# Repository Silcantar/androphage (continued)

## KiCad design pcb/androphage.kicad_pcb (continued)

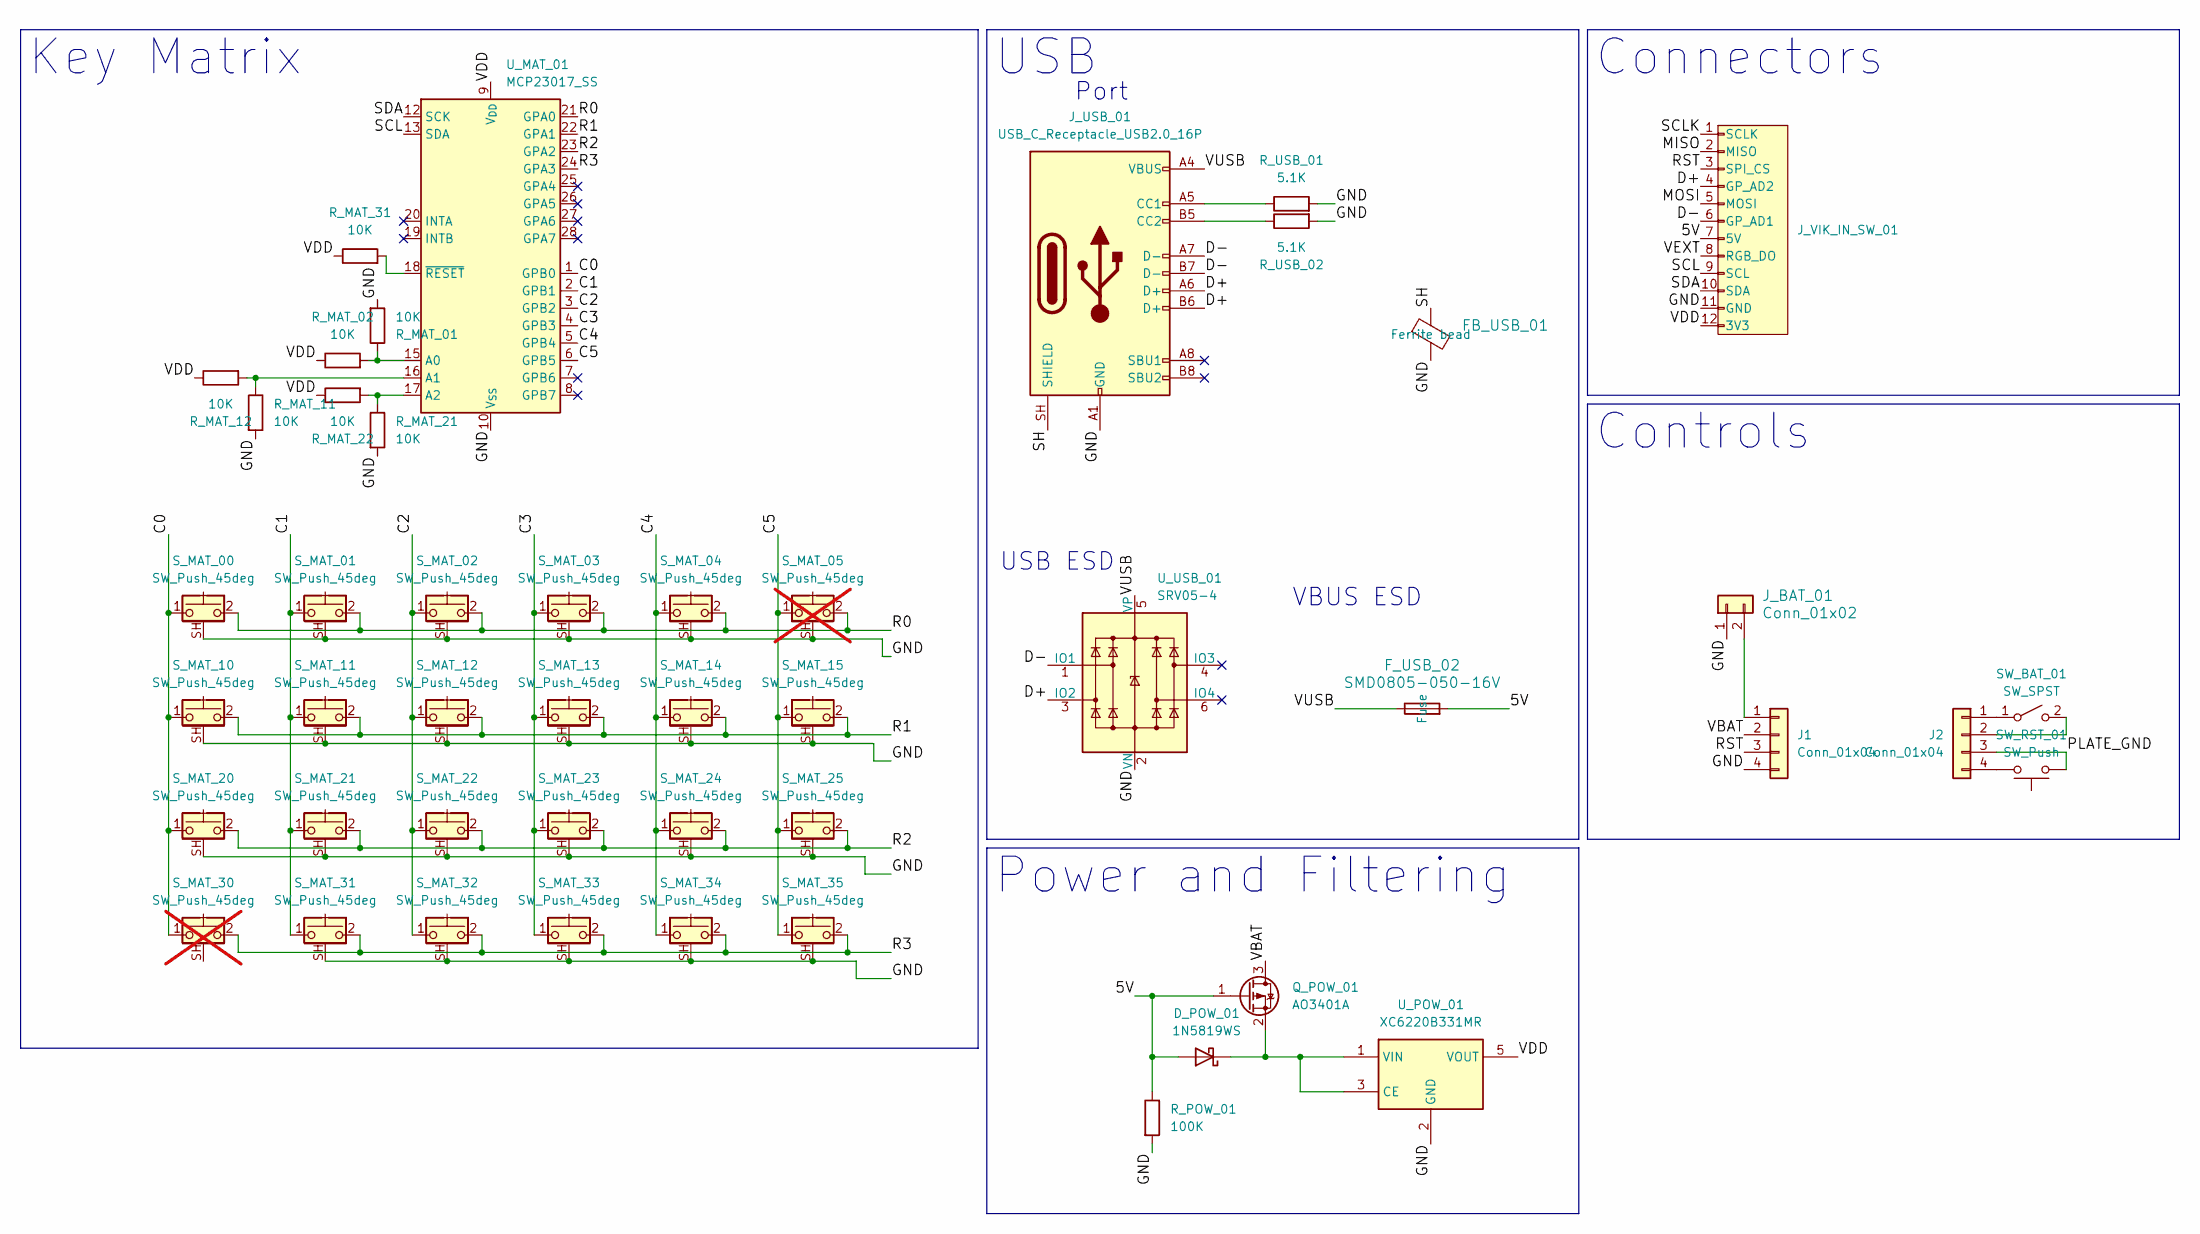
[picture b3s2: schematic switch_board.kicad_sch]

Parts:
D_POW_01: 1N5819WS; D_SOD-323
FB_USB_01: L_0805_2012Metric; LCSC Part Number C21286
F_USB_02: SMD0805-050-16V; Fuse_0805_2012Metric; Manufacturer Part Number SMD0805-050-16V; LCSC Part Number C2833485
J1, J2: Conn_01x04; PinHeader_1x04_P2.54mm_Vertical
J_BAT_01: Conn_01x02; JST_GH_SM02B-GHS-TB_1x02-1MP_P1.25mm_Horizontal
J_USB_01: USB_C_Receptacle_USB2.0_16P; USB_C_Receptacle_HRO_TYPE-C-31-M-12
J_VIK_IN_SW_01: vik-module-connector; vik-module-connector-horizontal
Q_POW_01: AO3401A; SOT-23
R_MAT_01, R_MAT_02, R_MAT_11, R_MAT_12, R_MAT_21, R_MAT_22, R_MAT_31: 10K; R_0201_0603Metric_Pad0.64x0.40mm_HandSolder
R_POW_01: 100K; R_0201_0603Metric_Pad0.64x0.40mm_HandSolder
R_USB_01, R_USB_02: 5.1K; R_0201_0603Metric_Pad0.64x0.40mm_HandSolder
SW_BAT_01: SW_SPST; AS11CH
SW_RST_01: SW_Push; SW_Push_1P1T_NO_E-Switch_TL3301NxxxxxG
S_MAT_00, S_MAT_01, S_MAT_02, S_MAT_03, S_MAT_04, S_MAT_10, S_MAT_11, S_MAT_12, S_MAT_13, S_MAT_14, S_MAT_15, S_MAT_20, S_MAT_21, S_MAT_22, S_MAT_23, S_MAT_24, S_MAT_25, S_MAT_31, S_MAT_32, S_MAT_33, S_MAT_34, S_MAT_35: SW_Push_45deg; SW_Kailh_Choc_V1V2_HotSwap_PTH_Double
S_MAT_05, S_MAT_30: SW_Push_45deg; SW_Kailh_Choc_V1V2_HotSwap_PTH_Double; not fitted
U_MAT_01: MCP23017_SS; SSOP-28_5.3x10.2mm_P0.65mm
U_POW_01: XC6220B331MR; SOT-23-5
U_USB_01: SRV05-4; SOT-23-6

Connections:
/Switch_Board/5V: D_POW_01.2 (A), F_USB_02.2, J_VIK_IN_SW_01.7 (5V), Q_POW_01.1 (G), R_POW_01.1
/Switch_Board/C0: S_MAT_00.1, S_MAT_10.1, S_MAT_20.1, S_MAT_30.1, U_MAT_01.1 (GPB0)
/Switch_Board/C1: S_MAT_01.1, S_MAT_11.1, S_MAT_21.1, S_MAT_31.1, U_MAT_01.2 (GPB1)
/Switch_Board/C2: S_MAT_02.1, S_MAT_12.1, S_MAT_22.1, S_MAT_32.1, U_MAT_01.3 (GPB2)
/Switch_Board/C3: S_MAT_03.1, S_MAT_13.1, S_MAT_23.1, S_MAT_33.1, U_MAT_01.4 (GPB3)
/Switch_Board/C4: S_MAT_04.1, S_MAT_14.1, S_MAT_24.1, S_MAT_34.1, U_MAT_01.5 (GPB4)
/Switch_Board/C5: S_MAT_05.1, S_MAT_15.1, S_MAT_25.1, S_MAT_35.1, U_MAT_01.6 (GPB5)
/Switch_Board/D+: J_USB_01.A6 (D+), J_USB_01.B6 (D+), J_VIK_IN_SW_01.4 (GP_AD2), U_USB_01.3 (IO2)
/Switch_Board/D-: J_USB_01.A7 (D-), J_USB_01.B7 (D-), J_VIK_IN_SW_01.6 (GP_AD1), U_USB_01.1 (IO1)
/Switch_Board/GND: FB_USB_01.2, J1.4, J_BAT_01.1, J_USB_01.A1 (GND), J_USB_01.A12 (GND), J_USB_01.B1 (GND), J_USB_01.B12 (GND), J_VIK_IN_SW_01.11 (GND), R_MAT_01.2, R_MAT_11.2, R_MAT_21.2, R_POW_01.2, R_USB_01.2, R_USB_02.2, S_MAT_00.SH (B), S_MAT_01.SH (B), S_MAT_02.SH (B), S_MAT_03.SH (B), S_MAT_04.SH (B), S_MAT_05.SH (B), S_MAT_10.SH (B), S_MAT_11.SH (B), S_MAT_12.SH (B), S_MAT_13.SH (B), S_MAT_14.SH (B), S_MAT_15.SH (B), S_MAT_20.SH (B), S_MAT_21.SH (B), S_MAT_22.SH (B), S_MAT_23.SH (B), S_MAT_24.SH (B), S_MAT_25.SH (B), S_MAT_31.SH (B), S_MAT_32.SH (B), S_MAT_33.SH (B), S_MAT_34.SH (B), S_MAT_35.SH (B), U_MAT_01.10 (V_{SS}), U_POW_01.2 (GND), U_USB_01.2 (VN)
/Switch_Board/MISO: J_VIK_IN_SW_01.2 (MISO)
/Switch_Board/MOSI: J_VIK_IN_SW_01.5 (MOSI)
/Switch_Board/PLATE_GND: J2.3, SW_RST_01.1
/Switch_Board/R0: S_MAT_00.2, S_MAT_01.2, S_MAT_02.2, S_MAT_03.2, S_MAT_04.2, S_MAT_05.2, U_MAT_01.21 (GPA0)
/Switch_Board/R1: S_MAT_10.2, S_MAT_11.2, S_MAT_12.2, S_MAT_13.2, S_MAT_14.2, S_MAT_15.2, U_MAT_01.22 (GPA1)
/Switch_Board/R2: S_MAT_20.2, S_MAT_21.2, S_MAT_22.2, S_MAT_23.2, S_MAT_24.2, S_MAT_25.2, U_MAT_01.23 (GPA2)
/Switch_Board/R3: S_MAT_30.2, S_MAT_31.2, S_MAT_32.2, S_MAT_33.2, S_MAT_34.2, S_MAT_35.2, U_MAT_01.24 (GPA3)
/Switch_Board/RST: J1.3, J_VIK_IN_SW_01.3 (SPI_CS)
/Switch_Board/SCL: J_VIK_IN_SW_01.9 (SCL), U_MAT_01.13 (SDA)
/Switch_Board/SCLK: J_VIK_IN_SW_01.1 (SCLK)
/Switch_Board/SDA: J_VIK_IN_SW_01.10 (SDA), U_MAT_01.12 (SCK)
/Switch_Board/SH: FB_USB_01.1, J_USB_01.SH (SHIELD)
/Switch_Board/VBAT: J1.2, Q_POW_01.3 (D)
/Switch_Board/VDD: J_VIK_IN_SW_01.12 (3V3), R_MAT_02.1, R_MAT_12.1, R_MAT_22.1, R_MAT_31.1, U_MAT_01.9 (V_{DD}), U_POW_01.5 (VOUT)
/Switch_Board/VEXT: J_VIK_IN_SW_01.8 (RGB_DO)
/Switch_Board/VUSB: F_USB_02.1, J_USB_01.A4 (VBUS), J_USB_01.A9 (VBUS), J_USB_01.B4 (VBUS), J_USB_01.B9 (VBUS), U_USB_01.5 (VP)
unnamed: D_POW_01.1 (K), Q_POW_01.2 (S), U_POW_01.1 (VIN), U_POW_01.3 (CE)
unnamed: J1.1, J_BAT_01.2
unnamed: J2.1, SW_BAT_01.1 (A)
unnamed: J2.2, SW_BAT_01.2 (B)
unnamed: J2.4, SW_RST_01.2
unnamed: J_USB_01.A5 (CC1), R_USB_01.1
unnamed: J_USB_01.B5 (CC2), R_USB_02.1
unnamed: R_MAT_01.1, R_MAT_02.2, U_MAT_01.15 (A0)
unnamed: R_MAT_11.1, R_MAT_12.2, U_MAT_01.16 (A1)
unnamed: R_MAT_21.1, R_MAT_22.2, U_MAT_01.17 (A2)
unnamed: R_MAT_31.2, U_MAT_01.18 (~RESET)

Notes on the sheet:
USB ESD
Port
VBUS ESD
Connectors
USB
Power and Filtering
Key Matrix
Controls

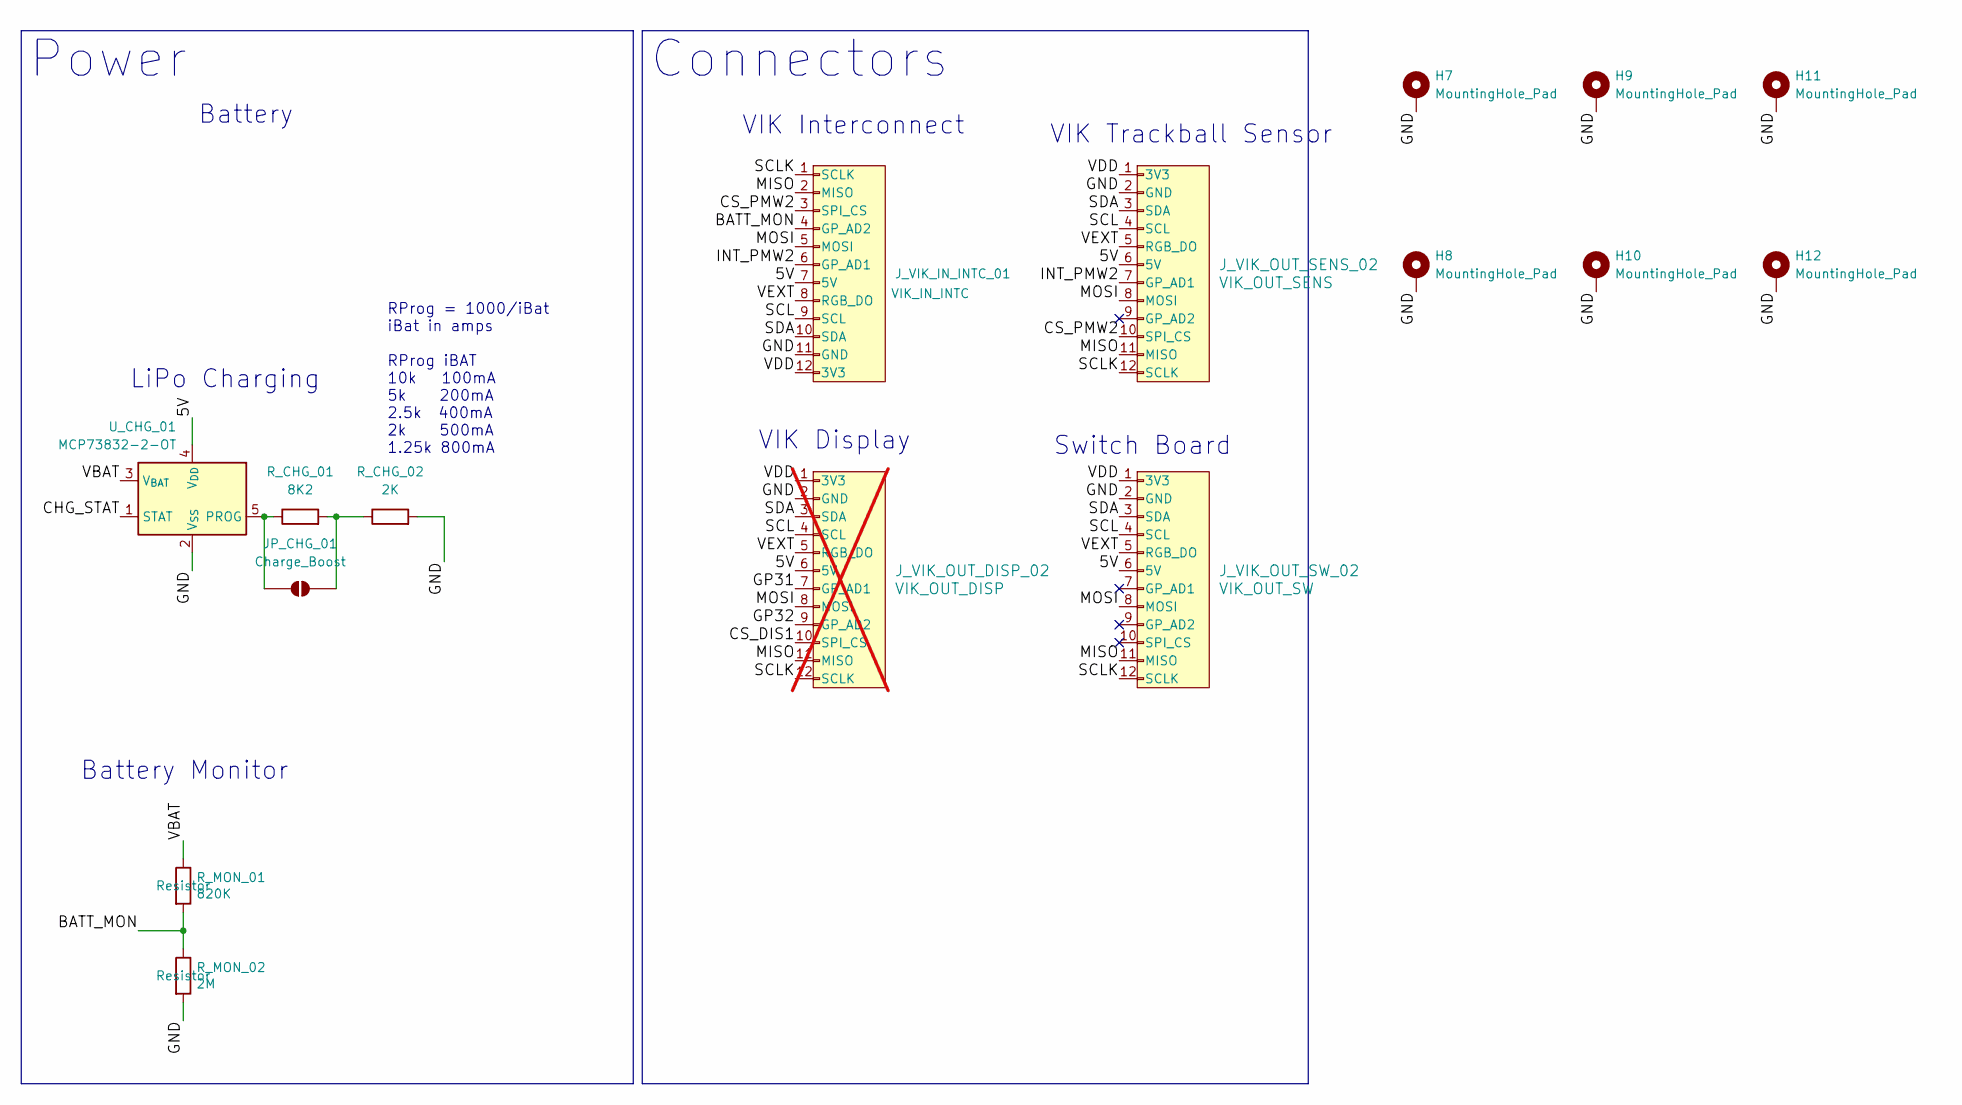
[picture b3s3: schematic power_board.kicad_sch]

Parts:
H7, H8, H9, H10, H11, H12: MountingHole_Pad; MountingHole_2.2mm_M2_Pad
JP_CHG_01: Charge_Boost; SolderJumper-2_P1.3mm_Open_RoundedPad1.0x1.5mm
J_VIK_IN_INTC_01: vik-module-connector; vik-module-connector-horizontal
J_VIK_OUT_DISP_02: VIK_OUT_DISP; vik-keyboard-connector-horizontal; not fitted
J_VIK_OUT_SENS_02: VIK_OUT_SENS; vik-keyboard-connector-horizontal
J_VIK_OUT_SW_02: VIK_OUT_SW; vik-keyboard-connector-horizontal
R_CHG_01: 8K2; R_0201_0603Metric_Pad0.64x0.40mm_HandSolder
R_CHG_02: 2K; R_0201_0603Metric_Pad0.64x0.40mm_HandSolder
R_MON_01: 820K; R_0603_1608Metric
R_MON_02: 2M; R_0603_1608Metric
U_CHG_01: MCP73832-2-OT; SOT-23-5

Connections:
/Power_Board/5V: J_VIK_IN_INTC_01.7 (5V), J_VIK_OUT_DISP_02.6 (5V), J_VIK_OUT_SENS_02.6 (5V), J_VIK_OUT_SW_02.6 (5V), U_CHG_01.4 (V_{DD})
/Power_Board/BATT_MON: J_VIK_IN_INTC_01.4 (GP_AD2), R_MON_01.2, R_MON_02.1
/Power_Board/CHG_STAT: U_CHG_01.1 (STAT)
/Power_Board/CS_PMW2: J_VIK_IN_INTC_01.3 (SPI_CS), J_VIK_OUT_SENS_02.10 (SPI_CS)
/Power_Board/GND: H7.1 (1_1), H8.1 (1_1), H9.1 (1_1), H10.1 (1_1), H11.1 (1_1), H12.1 (1_1), J_VIK_IN_INTC_01.11 (GND), J_VIK_OUT_DISP_02.2 (GND), J_VIK_OUT_SENS_02.2 (GND), J_VIK_OUT_SW_02.2 (GND), R_CHG_02.2, R_MON_02.2, U_CHG_01.2 (V_{SS})
/Power_Board/INT_PMW2: J_VIK_IN_INTC_01.6 (GP_AD1), J_VIK_OUT_SENS_02.7 (GP_AD1)
/Power_Board/MISO: J_VIK_IN_INTC_01.2 (MISO), J_VIK_OUT_DISP_02.11 (MISO), J_VIK_OUT_SENS_02.11 (MISO), J_VIK_OUT_SW_02.11 (MISO)
/Power_Board/MOSI: J_VIK_IN_INTC_01.5 (MOSI), J_VIK_OUT_DISP_02.8 (MOSI), J_VIK_OUT_SENS_02.8 (MOSI), J_VIK_OUT_SW_02.8 (MOSI)
/Power_Board/SCL: J_VIK_IN_INTC_01.9 (SCL), J_VIK_OUT_DISP_02.4 (SCL), J_VIK_OUT_SENS_02.4 (SCL), J_VIK_OUT_SW_02.4 (SCL)
/Power_Board/SCLK: J_VIK_IN_INTC_01.1 (SCLK), J_VIK_OUT_DISP_02.12 (SCLK), J_VIK_OUT_SENS_02.12 (SCLK), J_VIK_OUT_SW_02.12 (SCLK)
/Power_Board/SDA: J_VIK_IN_INTC_01.10 (SDA), J_VIK_OUT_DISP_02.3 (SDA), J_VIK_OUT_SENS_02.3 (SDA), J_VIK_OUT_SW_02.3 (SDA)
/Power_Board/VBAT: R_MON_01.1, U_CHG_01.3 (V_{BAT})
/Power_Board/VDD: J_VIK_IN_INTC_01.12 (3V3), J_VIK_OUT_DISP_02.1 (3V3), J_VIK_OUT_SENS_02.1 (3V3), J_VIK_OUT_SW_02.1 (3V3)
/Power_Board/VEXT: J_VIK_IN_INTC_01.8 (RGB_DO), J_VIK_OUT_DISP_02.5 (RGB_DO), J_VIK_OUT_SENS_02.5 (RGB_DO), J_VIK_OUT_SW_02.5 (RGB_DO)
unnamed: JP_CHG_01.1 (A), R_CHG_01.1, U_CHG_01.5 (PROG)
unnamed: JP_CHG_01.2 (B), R_CHG_01.2, R_CHG_02.1

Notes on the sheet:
Switch Board
RProg = 1000/iBat iBat in amps RProg iBAT 10k 100mA 5k 200mA 2.5k 400mA 2k 500mA 1.25k 800mA
Battery
VIK Interconnect
Battery Monitor
VIK Display
VIK Trackball Sensor
LiPo Charging
Connectors
Power

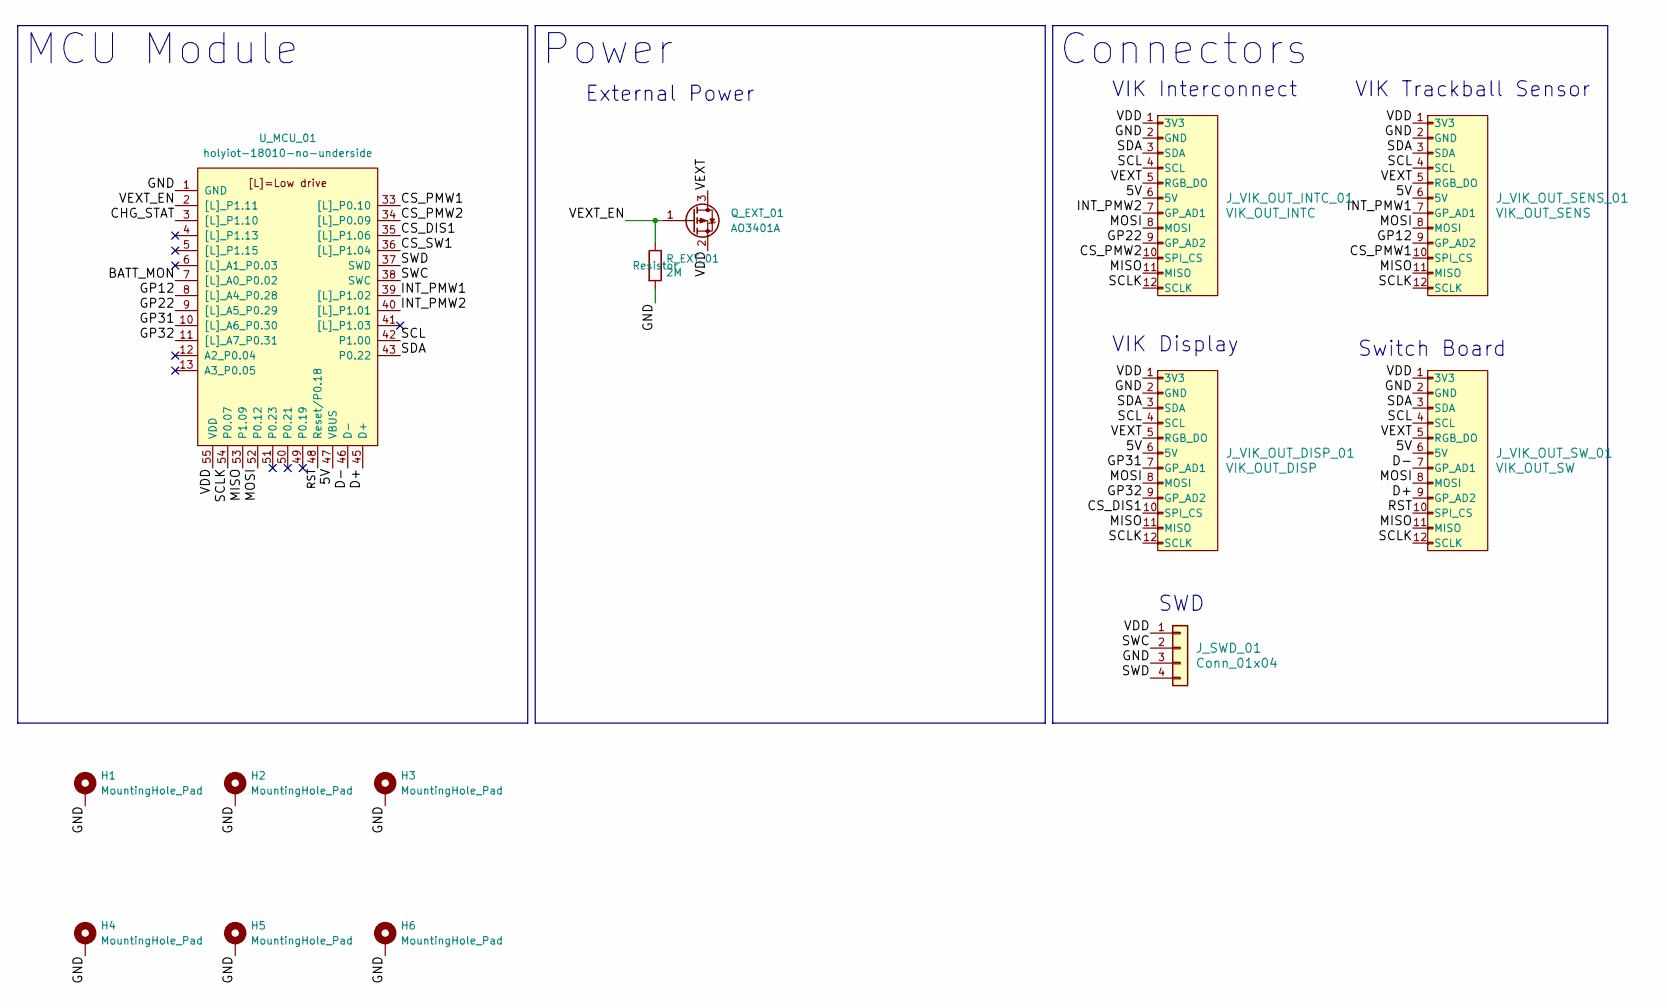
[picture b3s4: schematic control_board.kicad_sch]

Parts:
H1, H2, H3, H4, H5, H6: MountingHole_Pad; MountingHole_2.2mm_M2_Pad
J_SWD_01: Conn_01x04; PinHeader_1x04_P2.54mm_Vertical_SMD_Pin1Left
J_VIK_OUT_DISP_01: VIK_OUT_DISP; vik-keyboard-connector-horizontal
J_VIK_OUT_INTC_01: VIK_OUT_INTC; vik-keyboard-connector-horizontal
J_VIK_OUT_SENS_01: VIK_OUT_SENS; vik-keyboard-connector-horizontal
J_VIK_OUT_SW_01: VIK_OUT_SW; vik-keyboard-connector-horizontal
Q_EXT_01: AO3401A; SOT-23
R_EXT_01: 2M; R_0603_1608Metric
U_MCU_01: holyiot-18010-no-underside

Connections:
/Control_Board/5V: J_VIK_OUT_DISP_01.6 (5V), J_VIK_OUT_INTC_01.6 (5V), J_VIK_OUT_SENS_01.6 (5V), J_VIK_OUT_SW_01.6 (5V), U_MCU_01.47 (VBUS)
/Control_Board/BATT_MON: U_MCU_01.7 ([L]_A0_P0.02)
/Control_Board/CHG_STAT: U_MCU_01.3 ([L]_P1.10)
/Control_Board/CS_DIS1: J_VIK_OUT_DISP_01.10 (SPI_CS), U_MCU_01.35 ([L]_P1.06)
/Control_Board/CS_PMW1: J_VIK_OUT_SENS_01.10 (SPI_CS), U_MCU_01.33 ([L]_P0.10)
/Control_Board/CS_PMW2: J_VIK_OUT_INTC_01.10 (SPI_CS), U_MCU_01.34 ([L]_P0.09)
/Control_Board/CS_SW1: U_MCU_01.36 ([L]_P1.04)
/Control_Board/D+: J_VIK_OUT_SW_01.9 (GP_AD2), U_MCU_01.45 (D+)
/Control_Board/D-: J_VIK_OUT_SW_01.7 (GP_AD1), U_MCU_01.46 (D-)
/Control_Board/GND: H1.1 (1_1), H2.1 (1_1), H3.1 (1_1), H4.1 (1_1), H5.1 (1_1), H6.1 (1_1), J_SWD_01.3, J_VIK_OUT_DISP_01.2 (GND), J_VIK_OUT_INTC_01.2 (GND), J_VIK_OUT_SENS_01.2 (GND), J_VIK_OUT_SW_01.2 (GND), R_EXT_01.2, U_MCU_01.1 (GND), U_MCU_01.32 (GND), U_MCU_01.44 (GND)
/Control_Board/GP12: J_VIK_OUT_SENS_01.9 (GP_AD2), U_MCU_01.8 ([L]_A4_P0.28)
/Control_Board/GP22: J_VIK_OUT_INTC_01.9 (GP_AD2), U_MCU_01.9 ([L]_A5_P0.29)
/Control_Board/GP31: J_VIK_OUT_DISP_01.7 (GP_AD1), U_MCU_01.10 ([L]_A6_P0.30)
/Control_Board/GP32: J_VIK_OUT_DISP_01.9 (GP_AD2), U_MCU_01.11 ([L]_A7_P0.31)
/Control_Board/INT_PMW1: J_VIK_OUT_SENS_01.7 (GP_AD1), U_MCU_01.39 ([L]_P1.02)
/Control_Board/INT_PMW2: J_VIK_OUT_INTC_01.7 (GP_AD1), U_MCU_01.40 ([L]_P1.01)
/Control_Board/MISO: J_VIK_OUT_DISP_01.11 (MISO), J_VIK_OUT_INTC_01.11 (MISO), J_VIK_OUT_SENS_01.11 (MISO), J_VIK_OUT_SW_01.11 (MISO), U_MCU_01.53 (P1.09)
/Control_Board/MOSI: J_VIK_OUT_DISP_01.8 (MOSI), J_VIK_OUT_INTC_01.8 (MOSI), J_VIK_OUT_SENS_01.8 (MOSI), J_VIK_OUT_SW_01.8 (MOSI), U_MCU_01.52 (P0.12)
/Control_Board/RST: J_VIK_OUT_SW_01.10 (SPI_CS), U_MCU_01.48 (Reset/P0.18)
/Control_Board/SCL: J_VIK_OUT_DISP_01.4 (SCL), J_VIK_OUT_INTC_01.4 (SCL), J_VIK_OUT_SENS_01.4 (SCL), J_VIK_OUT_SW_01.4 (SCL), U_MCU_01.42 (P1.00)
/Control_Board/SCLK: J_VIK_OUT_DISP_01.12 (SCLK), J_VIK_OUT_INTC_01.12 (SCLK), J_VIK_OUT_SENS_01.12 (SCLK), J_VIK_OUT_SW_01.12 (SCLK), U_MCU_01.54 (P0.07)
/Control_Board/SDA: J_VIK_OUT_DISP_01.3 (SDA), J_VIK_OUT_INTC_01.3 (SDA), J_VIK_OUT_SENS_01.3 (SDA), J_VIK_OUT_SW_01.3 (SDA), U_MCU_01.43 (P0.22)
/Control_Board/SWC: J_SWD_01.2, U_MCU_01.38 (SWC)
/Control_Board/SWD: J_SWD_01.4, U_MCU_01.37 (SWD)
/Control_Board/VDD: J_SWD_01.1, J_VIK_OUT_DISP_01.1 (3V3), J_VIK_OUT_INTC_01.1 (3V3), J_VIK_OUT_SENS_01.1 (3V3), J_VIK_OUT_SW_01.1 (3V3), Q_EXT_01.2 (S), U_MCU_01.55 (VDD)
/Control_Board/VEXT: J_VIK_OUT_DISP_01.5 (RGB_DO), J_VIK_OUT_INTC_01.5 (RGB_DO), J_VIK_OUT_SENS_01.5 (RGB_DO), J_VIK_OUT_SW_01.5 (RGB_DO), Q_EXT_01.3 (D)
/Control_Board/VEXT_EN: Q_EXT_01.1 (G), R_EXT_01.1, U_MCU_01.2 ([L]_P1.11)

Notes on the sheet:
VIK Trackball Sensor
VIK Display
External Power
Switch Board
VIK Interconnect
SWD
Power
MCU Module
Connectors

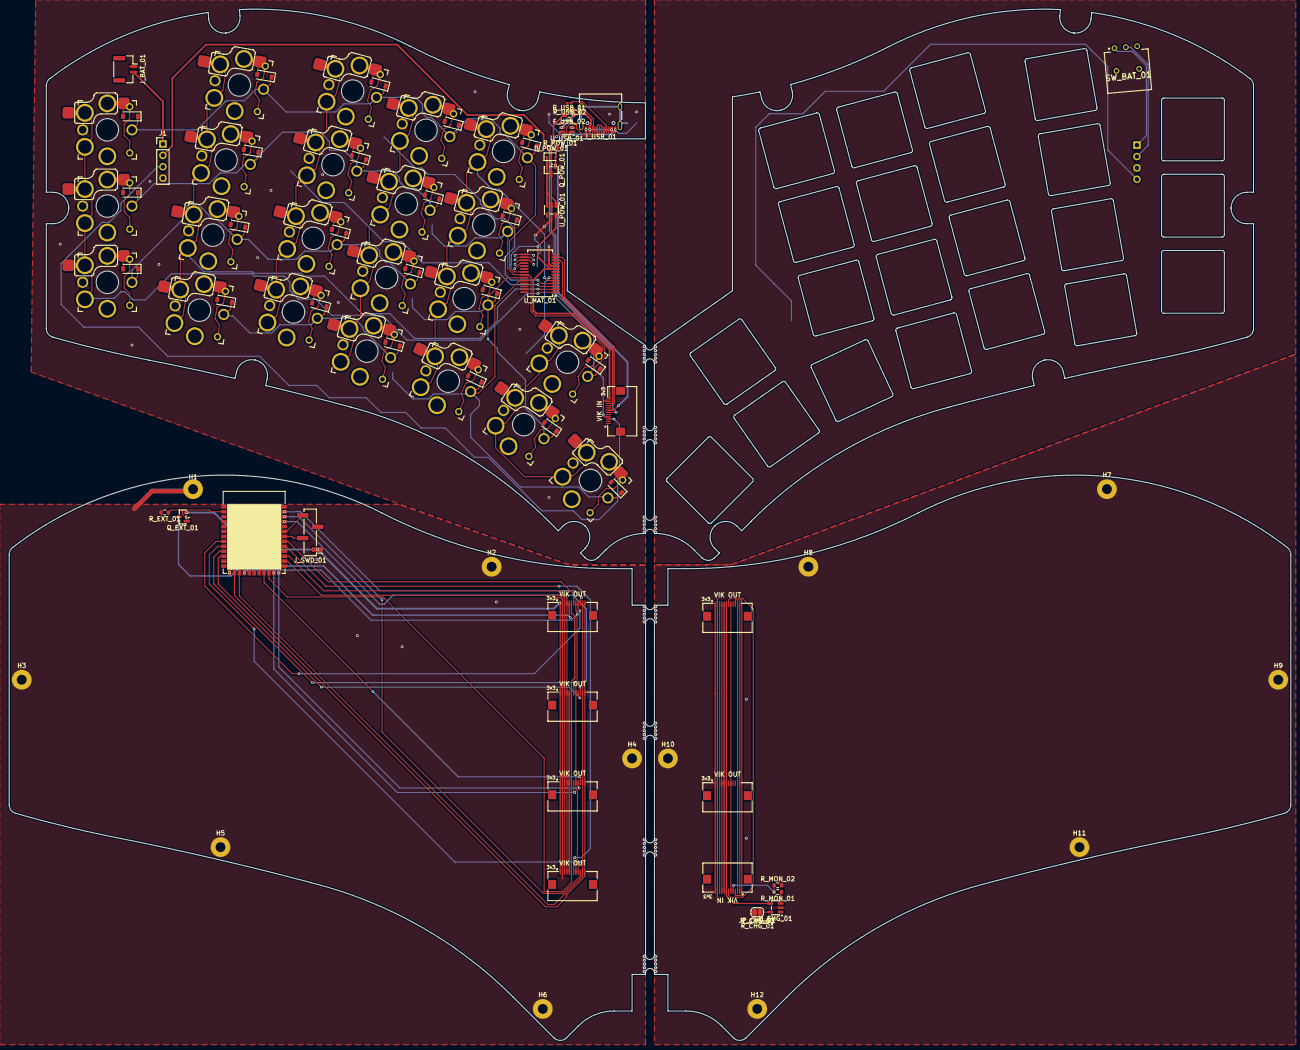
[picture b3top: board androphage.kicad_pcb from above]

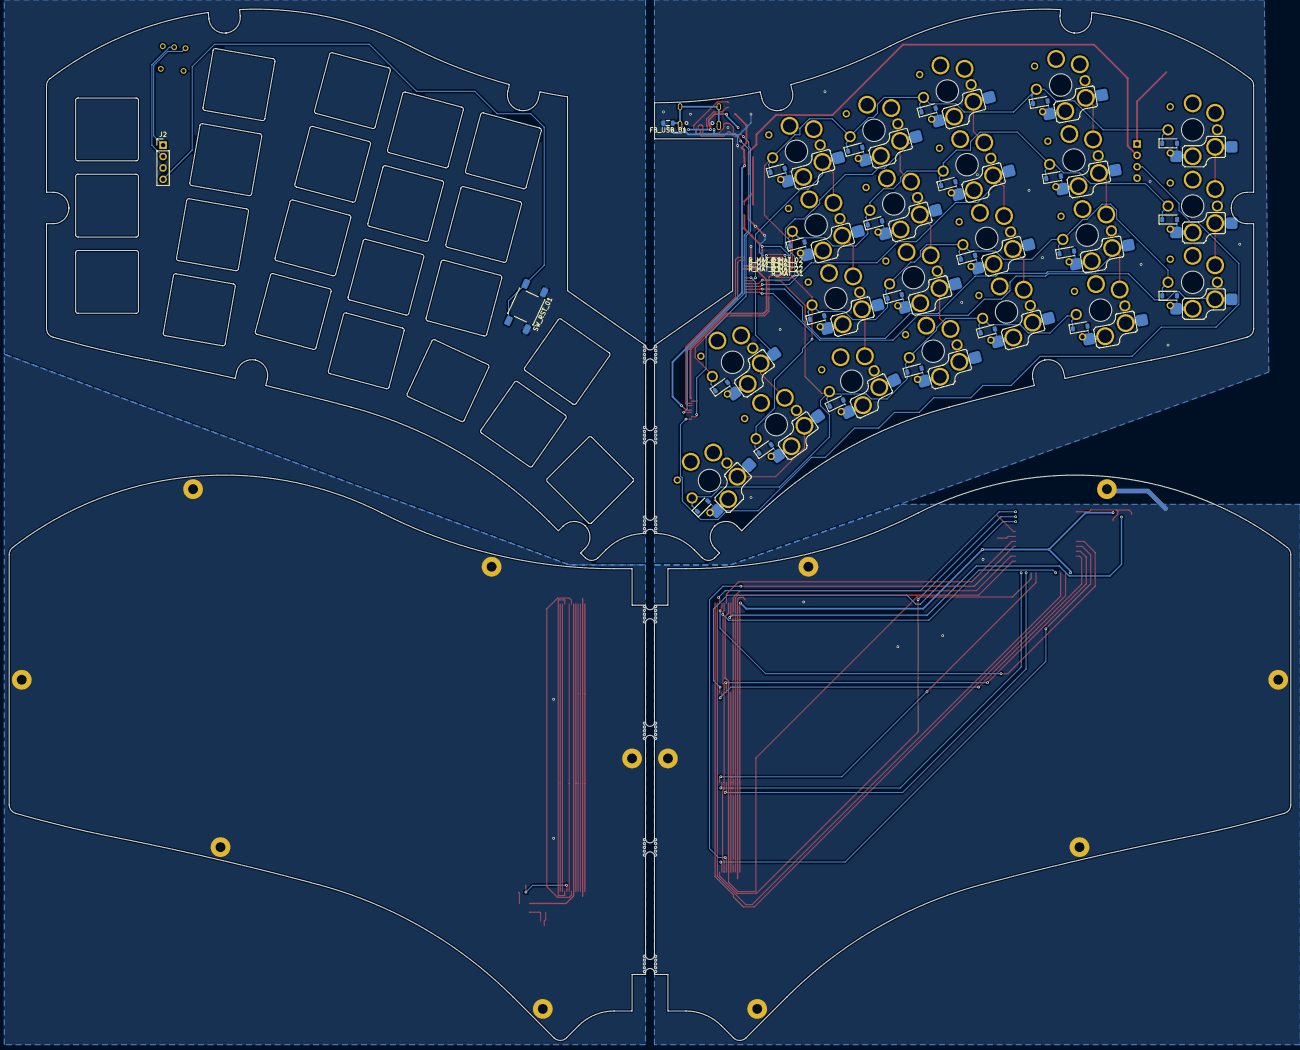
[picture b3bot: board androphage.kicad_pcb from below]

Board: 2 copper layers, 285.8 x 230.0 mm, 75 parts (10 on the bottom side), 72 nets.

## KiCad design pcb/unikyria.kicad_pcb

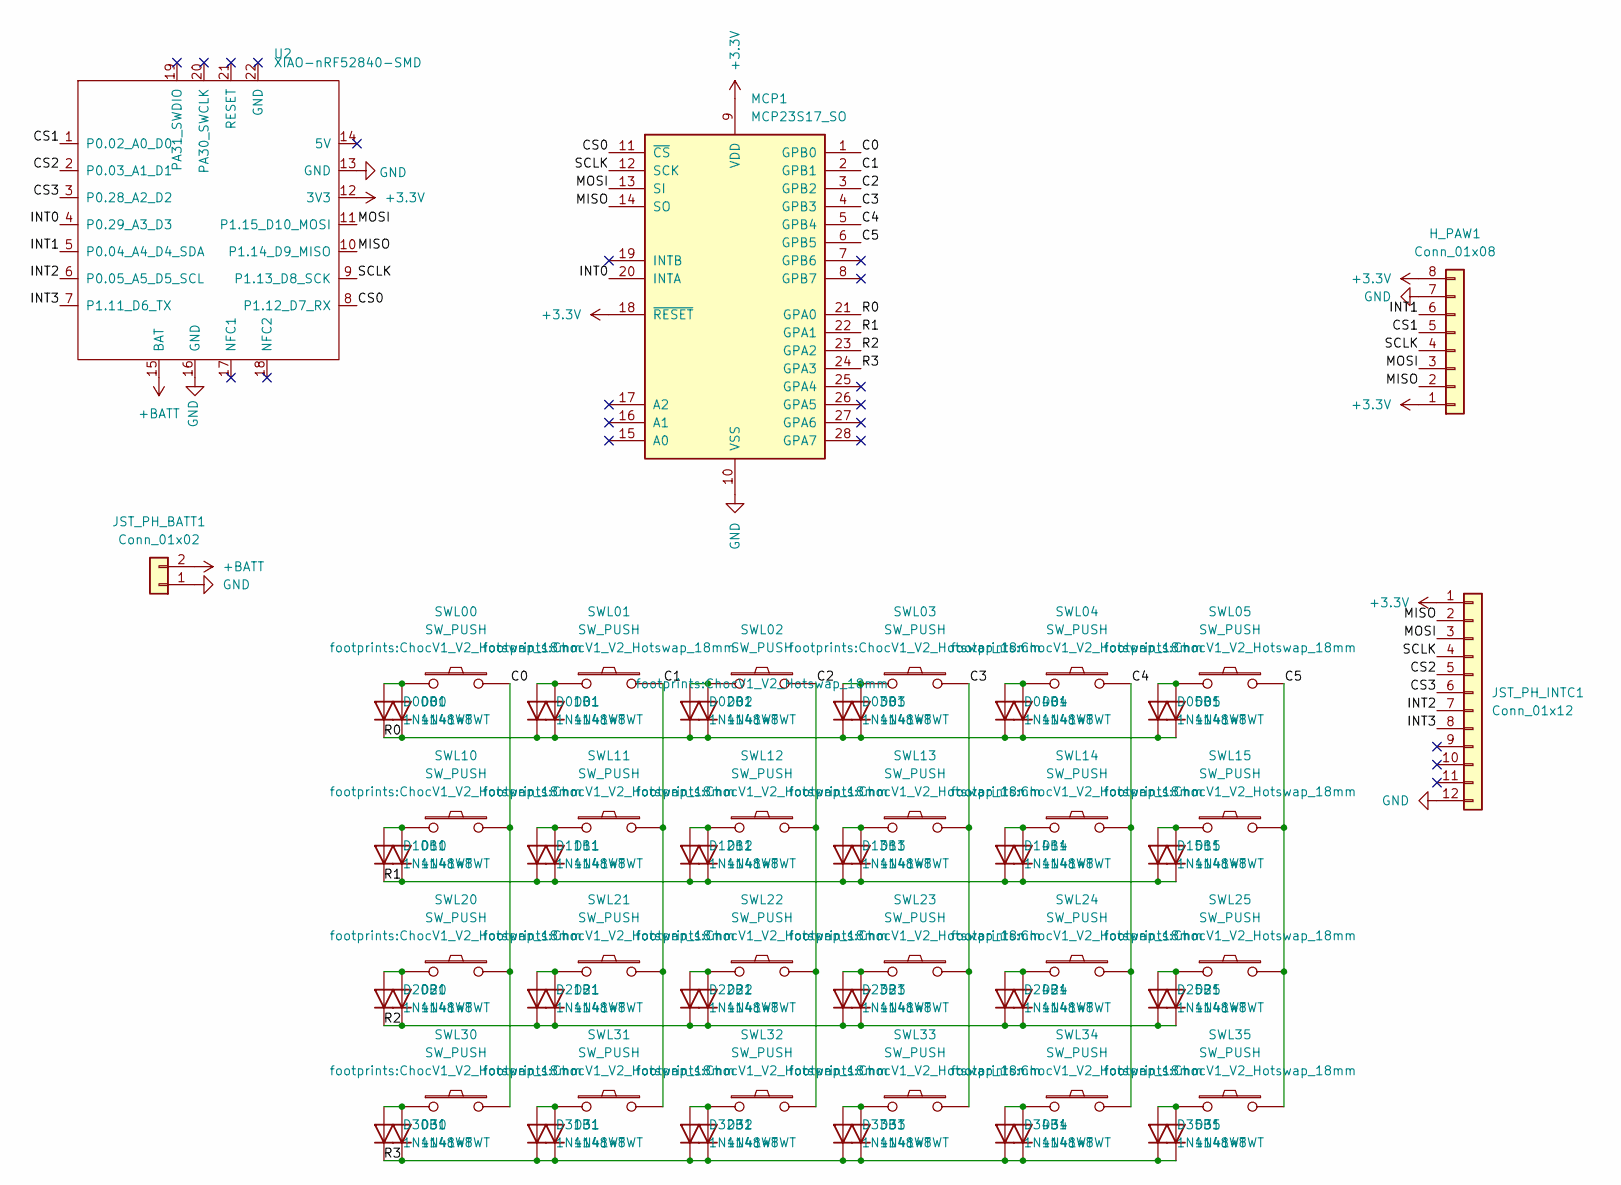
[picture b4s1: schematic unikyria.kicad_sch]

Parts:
D00, D00B1, D01, D01B1, D02, D02B1, D03, D03B1, D04, D04B1, D05, D05B1, D10, D10B1, D11, D11B1, D12, D12B1, D13, D13B1, D14, D14B1, D15, D15B1, D20, D20B1, D21, D21B1, D22, D22B1, D23, D23B1, D24, D24B1, D25, D25B1, D30, D30B1, D31, D31B1, D32, D32B1, D33, D33B1, D34, D34B1, D35, D35B1: 1N4148WT; D_SOD-523
H_PAW1: Conn_01x08; PinHeader_1x08_P2.54mm_Horizontal
JST_PH_BATT1: Conn_01x02; JST_PH_S2B-PH-K_1x02_P2.00mm_Horizontal
JST_PH_INTC1: Conn_01x12; JST_PH_S12B-PH-K_1x12_P2.00mm_Horizontal
MCP1: MCP23S17_SO; SOIC-28W_7.5x17.9mm_P1.27mm
SWL00, SWL01, SWL02, SWL03, SWL04, SWL05, SWL10, SWL11, SWL12, SWL13, SWL14, SWL15, SWL20, SWL21, SWL22, SWL23, SWL24, SWL25, SWL30, SWL31, SWL32, SWL33, SWL34, SWL35: SW_PUSH; ChocV1_V2_Hotswap_18mm
U2: XIAO-nRF52840-SMD

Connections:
+3.3V: H_PAW1.1, H_PAW1.8, JST_PH_INTC1.1, MCP1.9 (VDD), MCP1.18 (~RESET), U2.12 (3V3)
+BATT: JST_PH_BATT1.2, U2.15 (BAT)
/C0: MCP1.1 (GPB0), SWL00.2, SWL10.2, SWL20.2, SWL30.2
/C1: MCP1.2 (GPB1), SWL01.2, SWL11.2, SWL21.2, SWL31.2
/C2: MCP1.3 (GPB2), SWL02.2, SWL12.2, SWL22.2, SWL32.2
/C3: MCP1.4 (GPB3), SWL03.2, SWL13.2, SWL23.2, SWL33.2
/C4: MCP1.5 (GPB4), SWL04.2, SWL14.2, SWL24.2, SWL34.2
/C5: MCP1.6 (GPB5), SWL05.2, SWL15.2, SWL25.2, SWL35.2
/CS0: MCP1.11 (~CS), U2.8 (P1.12_D7_RX)
/CS1: H_PAW1.5, U2.1 (P0.02_A0_D0)
/CS2: JST_PH_INTC1.5, U2.2 (P0.03_A1_D1)
/CS3: JST_PH_INTC1.6, U2.3 (P0.28_A2_D2)
/INT0: MCP1.20 (INTA), U2.4 (P0.29_A3_D3)
/INT1: H_PAW1.6, U2.5 (P0.04_A4_D4_SDA)
/INT2: JST_PH_INTC1.7, U2.6 (P0.05_A5_D5_SCL)
/INT3: JST_PH_INTC1.8, U2.7 (P1.11_D6_TX)
/MISO: H_PAW1.2, JST_PH_INTC1.2, MCP1.14 (SO), U2.10 (P1.14_D9_MISO)
/MOSI: H_PAW1.3, JST_PH_INTC1.3, MCP1.13 (SI), U2.11 (P1.15_D10_MOSI)
/R0: D00.1 (K), D00B1.1 (K), D01.1 (K), D01B1.1 (K), D02.1 (K), D02B1.1 (K), D03.1 (K), D03B1.1 (K), D04.1 (K), D04B1.1 (K), D05.1 (K), D05B1.1 (K), MCP1.21 (GPA0)
/R1: D10.1 (K), D10B1.1 (K), D11.1 (K), D11B1.1 (K), D12.1 (K), D12B1.1 (K), D13.1 (K), D13B1.1 (K), D14.1 (K), D14B1.1 (K), D15.1 (K), D15B1.1 (K), MCP1.22 (GPA1)
/R2: D20.1 (K), D20B1.1 (K), D21.1 (K), D21B1.1 (K), D22.1 (K), D22B1.1 (K), D23.1 (K), D23B1.1 (K), D24.1 (K), D24B1.1 (K), D25.1 (K), D25B1.1 (K), MCP1.23 (GPA2)
/R3: D30.1 (K), D30B1.1 (K), D31.1 (K), D31B1.1 (K), D32.1 (K), D32B1.1 (K), D33.1 (K), D33B1.1 (K), D34.1 (K), D34B1.1 (K), D35.1 (K), D35B1.1 (K), MCP1.24 (GPA3)
/SCLK: H_PAW1.4, JST_PH_INTC1.4, MCP1.12 (SCK), U2.9 (P1.13_D8_SCK)
GND: H_PAW1.7, JST_PH_BATT1.1, JST_PH_INTC1.12, MCP1.10 (VSS), U2.13 (GND), U2.16 (GND)
unnamed: D00.2 (A), D00B1.2 (A), SWL00.1
unnamed: D01.2 (A), D01B1.2 (A), SWL01.1
unnamed: D02.2 (A), D02B1.2 (A), SWL02.1
unnamed: D03.2 (A), D03B1.2 (A), SWL03.1
unnamed: D04.2 (A), D04B1.2 (A), SWL04.1
unnamed: D05.2 (A), D05B1.2 (A), SWL05.1
unnamed: D10.2 (A), D10B1.2 (A), SWL10.1
unnamed: D11.2 (A), D11B1.2 (A), SWL11.1
unnamed: D12.2 (A), D12B1.2 (A), SWL12.1
unnamed: D13.2 (A), D13B1.2 (A), SWL13.1
unnamed: D14.2 (A), D14B1.2 (A), SWL14.1
unnamed: D15.2 (A), D15B1.2 (A), SWL15.1
unnamed: D20.2 (A), D20B1.2 (A), SWL20.1
unnamed: D21.2 (A), D21B1.2 (A), SWL21.1
unnamed: D22.2 (A), D22B1.2 (A), SWL22.1
unnamed: D23.2 (A), D23B1.2 (A), SWL23.1
unnamed: D24.2 (A), D24B1.2 (A), SWL24.1
unnamed: D25.2 (A), D25B1.2 (A), SWL25.1
unnamed: D30.2 (A), D30B1.2 (A), SWL30.1
unnamed: D31.2 (A), D31B1.2 (A), SWL31.1
unnamed: D32.2 (A), D32B1.2 (A), SWL32.1
unnamed: D33.2 (A), D33B1.2 (A), SWL33.1
unnamed: D34.2 (A), D34B1.2 (A), SWL34.1
unnamed: D35.2 (A), D35B1.2 (A), SWL35.1

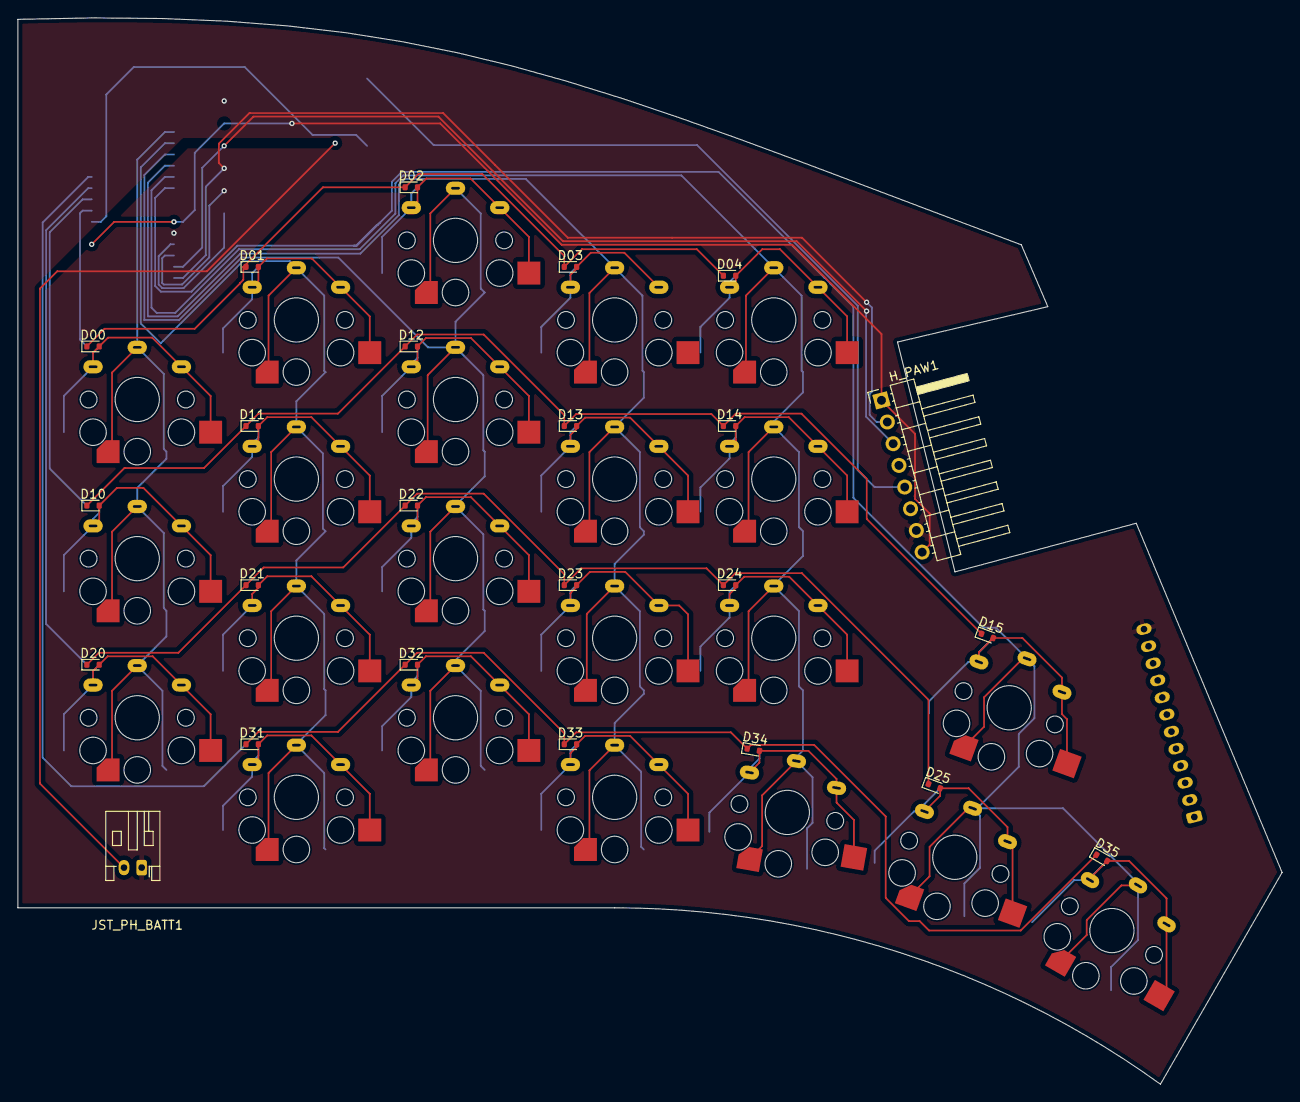
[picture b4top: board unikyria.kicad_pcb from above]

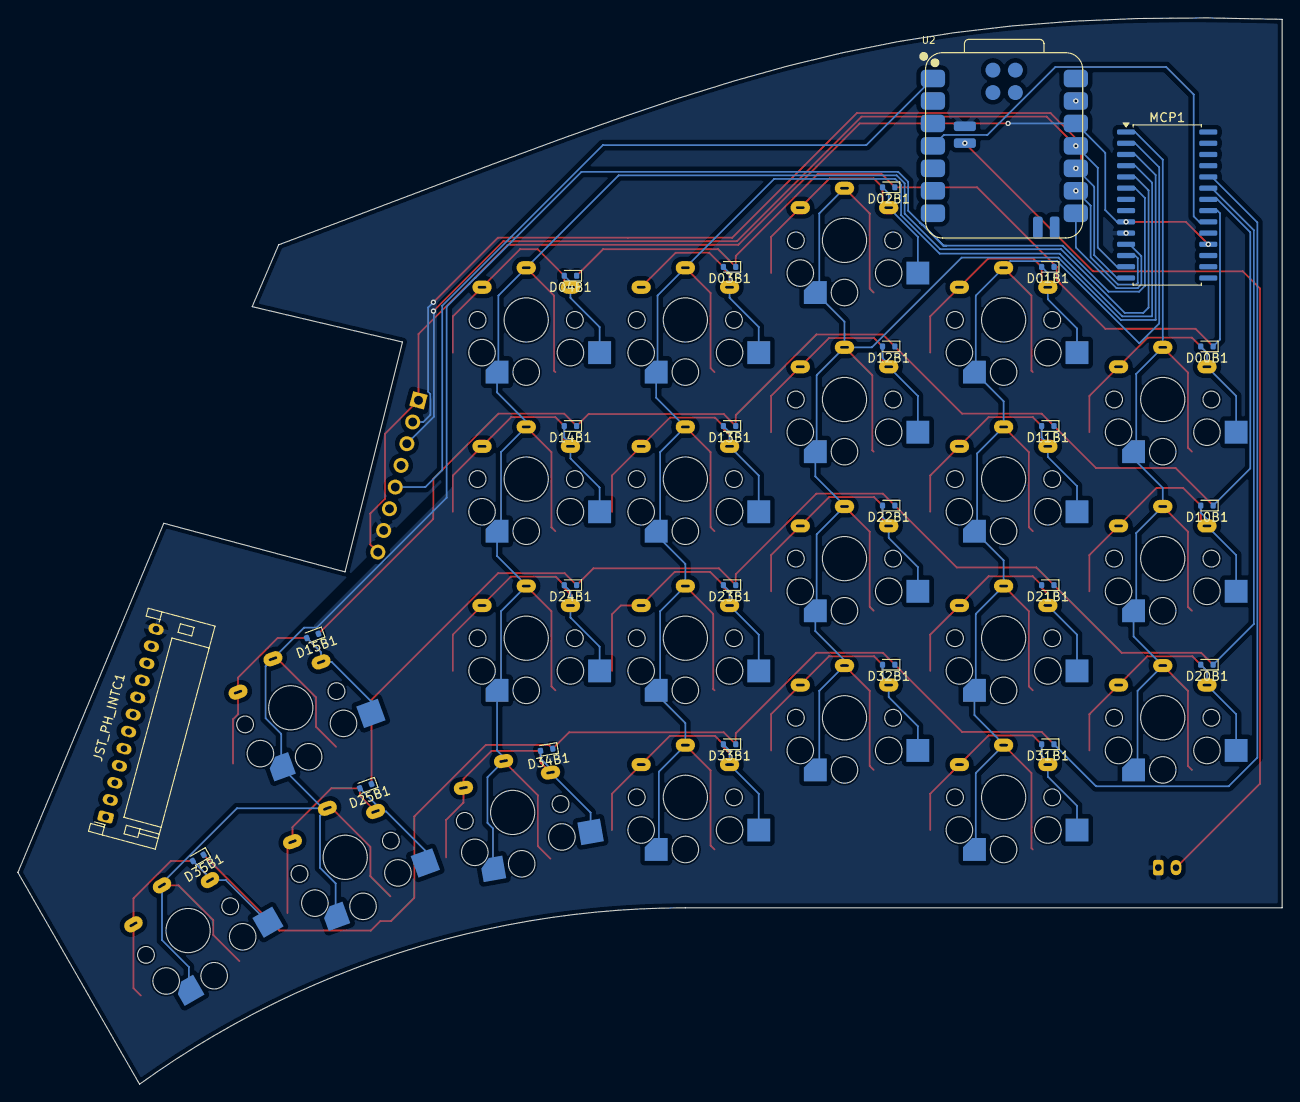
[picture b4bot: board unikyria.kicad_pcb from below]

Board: 2 copper layers, 143.0 x 120.6 mm, 71 parts (25 on the bottom side), 46 nets.
